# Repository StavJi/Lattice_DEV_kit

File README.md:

# Lattice DEV kit

Devkit is tested with cheap programmer from ebay. To find it try to use catchphrase ```ispDOWNLOAD Cable HW-USBN-2A```.

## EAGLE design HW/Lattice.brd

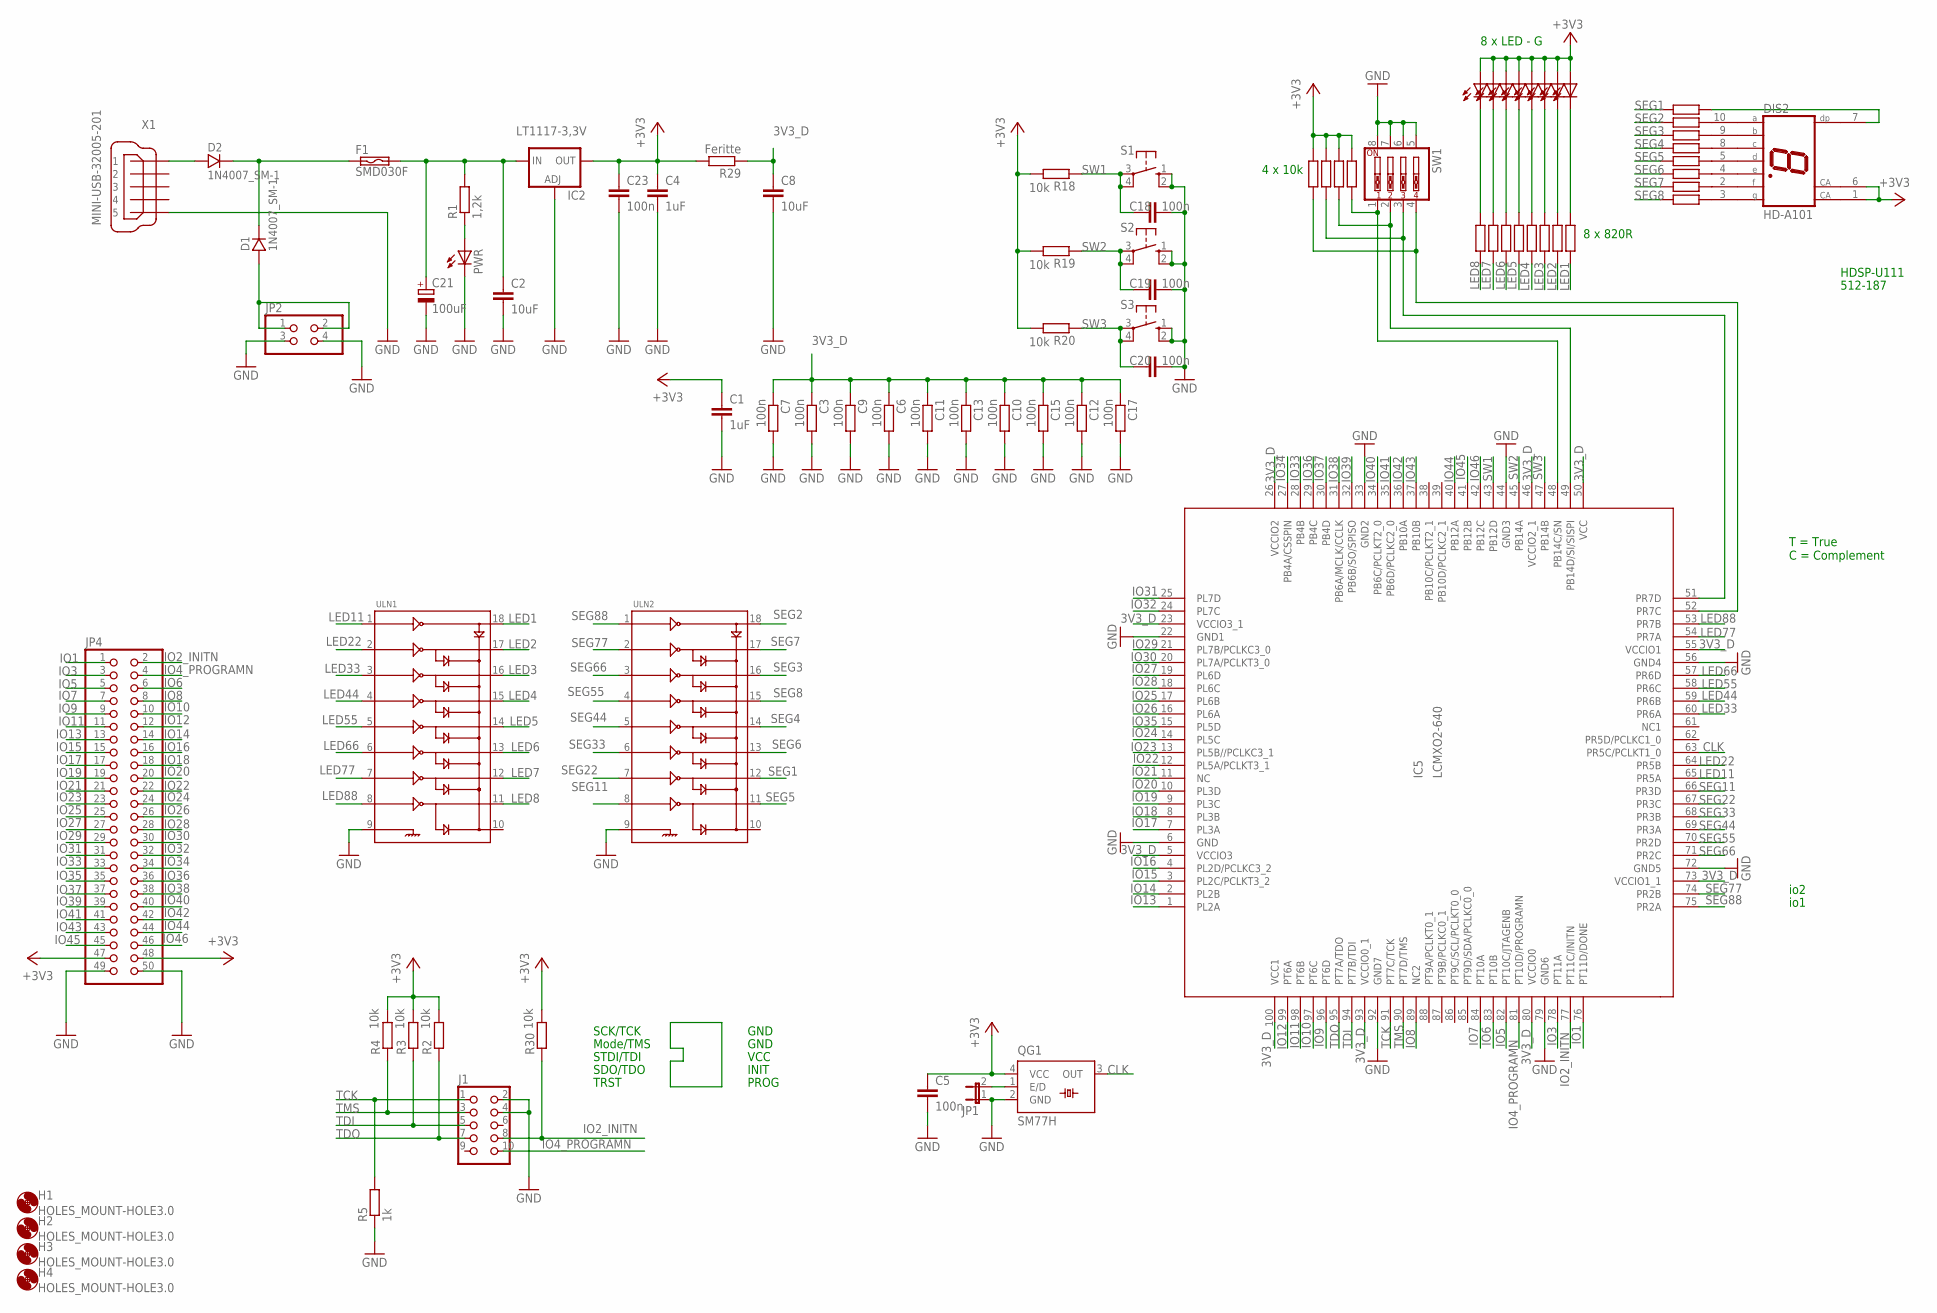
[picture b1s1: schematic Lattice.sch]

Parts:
C1, C4: 1uF; C1206
C2, C8: 10uF; C1206
C3, C6, C7, C9, C10, C11, C12, C13, C15, C17: 100n; R0603
C5, C18, C19, C20, C23: 100n; C0805
C21: 100uF; 153CLV-0605
D1, D2: 1N4007_SM-1; SM-1
DIS2: HD-A101; HDSP-A
F1: SMD030F; SMD050F
H1, H2, H3, H4: HOLES_MOUNT-HOLE3.0; HOLES_3,0
IC2: LT1117-3,3V; SOT223
IC5: LCMXO2-640; LCMX02-640
J1: CON_HEADER_2X05-PTH+SHROUDED_A; PINSHRD_PTH_2X05
JP1: JP1E; JP1
JP2: PINHD-2X2; 2X02
JP4: PINHD-2X25; 2X25
LED1, LED2, LED3, LED4, LED5, LED6, LED7, LED8: LEDSMT1206; 1206
PWR: LEDSMT1206; 1206
QG1: SM77H
R1: 1,2k; R0805
R2, R3, R4, R18, R19, R20, R30: 10k; R0805
R5: 1k; R0805
R6, R7, R8, R9, R10, R11, R12, R13, R14, R15, R16, R17, R21, R22, R23, R24, R25, R26, R27, R28: R-EU_R0805; R0805
R29: Feritte; R0805
S1, S2, S3: 10-XX; B3F-10XX
SW1: SW_DIP-4; EDG-04
ULN1, ULN2: ULN2803SOIC; SO018
X1: MINI-USB-32005-201; 32005-201

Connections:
3V3_D: C3.1, C6.1, C7.1, C8.1, C9.1, C10.1, C11.1, C12.1, C13.1, C15.1, C17.1, IC5.5 (VCCIO3), IC5.23 (VCCIO3_1), IC5.26 (VCCIO2), IC5.46 (VCCIO2_1), IC5.50 (VCC), IC5.55 (VCCIO1), IC5.73 (VCCIO1_1), IC5.80 (VCCIO0), IC5.93 (VCCIO0_1), IC5.100 (VCC1), R29.1
+3V3: C1.1, C4.1, C5.1, C23.1, DIS2.1 (CA), DIS2.6 (CA), IC2.4 (OUT), JP4.47, JP4.48, LED1.A, LED2.A, LED3.A, LED4.A, LED5.A, LED6.A, LED7.A, LED8.A, QG1.4 (VCC), R2.2, R3.2, R4.2, R14.1, R15.1, R16.1, R17.1, R18.2, R19.2, R20.2, R29.2, R30.2
CLK: IC5.63 (PR5C/PCLKT1_0), QG1.3 (OUT)
GND: C1.2, C2.2, C3.2, C4.2, C5.2, C6.2, C7.2, C8.2, C9.2, C10.2, C11.2, C12.2, C13.2, C15.2, C17.2, C18.2, C19.2, C20.2, C21.-, C23.2, IC2.1 (ADJ), IC5.6 (GND), IC5.22 (GND1), IC5.33 (GND2), IC5.44 (GND3), IC5.56 (GND4), IC5.72 (GND5), IC5.79 (GND6), IC5.92 (GND7), J1.2, J1.4, JP1.1, JP2.3, JP2.4, JP4.49, JP4.50, PWR.C, QG1.2 (GND), R5.1, S1.1 (S), S1.2 (S1), S2.1 (S), S2.2 (S1), S3.1 (S), S3.2 (S1), SW1.5, SW1.6, SW1.7, SW1.8, ULN1.9, ULN2.9, X1.5
IO1: IC5.76 (PT11D/DONE), JP4.1
IO2_INITN: IC5.77 (PT11C/INITN), J1.8, JP4.2, R30.1
IO3: IC5.78 (PT11A), JP4.3
IO4_PROGRAMN: IC5.81 (PT10D/PROGRAMN), J1.10, JP4.4
IO5: IC5.82 (PT10C/JTAGENB), JP4.5
IO6: IC5.83 (PT10B), JP4.6
IO7: IC5.84 (PT10A), JP4.7
IO8: IC5.89 (NC2), JP4.8
IO9: IC5.96 (PT6D), JP4.9
IO10: IC5.97 (PT6C), JP4.10
IO11: IC5.98 (PT6B), JP4.11
IO12: IC5.99 (PT6A), JP4.12
IO13: IC5.1 (PL2A), JP4.13
IO14: IC5.2 (PL2B), JP4.14
IO15: IC5.3 (PL2C/PCLKT3_2), JP4.15
IO16: IC5.4 (PL2D/PCLKC3_2), JP4.16
IO17: IC5.7 (PL3A), JP4.17
IO18: IC5.8 (PL3B), JP4.18
IO19: IC5.9 (PL3C), JP4.19
IO20: IC5.10 (PL3D), JP4.20
IO21: IC5.11 (NC), JP4.21
IO22: IC5.12 (PL5A/PCLKT3_1), JP4.22
IO23: IC5.13 (PL5B//PCLKC3_1), JP4.23
IO24: IC5.14 (PL5C), JP4.24
IO25: IC5.17 (PL6B), JP4.25
IO26: IC5.16 (PL6A), JP4.26
IO27: IC5.19 (PL6D), JP4.27
IO28: IC5.18 (PL6C), JP4.28
IO29: IC5.21 (PL7B/PCLKC3_0), JP4.29
IO30: IC5.20 (PL7A/PCLKT3_0), JP4.30
IO31: IC5.25 (PL7D), JP4.31
IO32: IC5.24 (PL7C), JP4.32
IO33: IC5.28 (PB4B), JP4.33
IO34: IC5.27 (PB4A/CSSPIN), JP4.34
IO35: IC5.15 (PL5D), JP4.35
IO36: IC5.29 (PB4C), JP4.36
IO37: IC5.30 (PB4D), JP4.37
IO38: IC5.31 (PB6A/MCLK/CCLK), JP4.38
IO39: IC5.32 (PB6B/SO/SPISO), JP4.39
IO40: IC5.34 (PB6C/PCLKT2_0), JP4.40
IO41: IC5.35 (PB6D/PCLKC2_0), JP4.41
IO42: IC5.36 (PB10A), JP4.42
IO43: IC5.37 (PB10B), JP4.43
IO44: IC5.40 (PB12A), JP4.44
IO45: IC5.41 (PB12B), JP4.45
IO46: IC5.42 (PB12C), JP4.46
LED1: R6.1, ULN1.18
LED2: R7.1, ULN1.17
LED3: R8.1, ULN1.16
LED4: R9.1, ULN1.15
LED5: R10.1, ULN1.14
LED6: R11.1, ULN1.13
LED7: R12.1, ULN1.12
LED8: R13.1, ULN1.11
LED11: IC5.65 (PR5A), ULN1.1
LED22: IC5.64 (PR5B), ULN1.2
LED33: IC5.60 (PR6A), ULN1.3
LED44: IC5.59 (PR6B), ULN1.4
LED55: IC5.58 (PR6C), ULN1.5
LED66: IC5.57 (PR6D), ULN1.6
LED77: IC5.54 (PR7A), ULN1.7
LED88: IC5.53 (PR7B), ULN1.8
unnamed: PWR.A, R1.1
unnamed: C2.1, C21.+, F1.2, IC2.3 (IN), R1.2
unnamed: JP1.2, QG1.1 (E/D)
unnamed: IC5.48 (PB14C/SN), R14.2, SW1.1
unnamed: DIS2.10 (A), R22.1
unnamed: DIS2.9 (B), R23.1
unnamed: DIS2.8 (C), R24.1
unnamed: DIS2.5 (D), R25.1
unnamed: DIS2.4 (E), R26.1
unnamed: LED1.C, R13.2
unnamed: LED2.C, R12.2
unnamed: LED3.C, R11.2
unnamed: LED4.C, R10.2
unnamed: LED5.C, R9.2
unnamed: LED6.C, R8.2
unnamed: LED7.C, R7.2
unnamed: LED8.C, R6.2
unnamed: DIS2.2 (F), R27.1
unnamed: IC5.51 (PR7D), R16.2, SW1.3
unnamed: DIS2.3 (G), R28.1
unnamed: DIS2.7 (DP), R21.1
unnamed: IC5.49 (PB14D/SI/SISPI), R15.2, SW1.2
unnamed: D1.A, JP2.1, JP2.2
unnamed: IC5.52 (PR7C), R17.2, SW1.4
unnamed: D1.K, D2.K, F1.1
unnamed: D2.A, X1.1
SEG1: R21.2, ULN2.12
SEG2: R22.2, ULN2.18
SEG3: R23.2, ULN2.16
SEG4: R24.2, ULN2.14
SEG5: R25.2, ULN2.11
SEG6: R26.2, ULN2.13
SEG7: R27.2, ULN2.17
SEG8: R28.2, ULN2.15
SEG11: IC5.66 (PR3D), ULN2.8
SEG22: IC5.67 (PR3C), ULN2.7
SEG33: IC5.68 (PR3B), ULN2.6
SEG44: IC5.69 (PR3A), ULN2.5
SEG55: IC5.70 (PR2D), ULN2.4
SEG66: IC5.71 (PR2C), ULN2.3
SEG77: IC5.74 (PR2B), ULN2.2
SEG88: IC5.75 (PR2A), ULN2.1
SW1: C18.1, IC5.43 (PB12D), R18.1, S1.3, S1.4 (P1)
SW2: C19.1, IC5.45 (PB14A), R19.1, S2.3, S2.4 (P1)
SW3: C20.1, IC5.47 (PB14B), R20.1, S3.3, S3.4 (P1)
TCK: IC5.91 (PT7C/TCK), J1.1, R5.2
TDI: IC5.94 (PT7B/TDI), J1.5, R3.1
TDO: IC5.95 (PT7A/TDO), J1.7, R2.1
TMS: IC5.90 (PT7D/TMS), J1.3, R4.1

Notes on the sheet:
8 x 820R
4 x 10k
8 x LED - G
T = True C = Complement
HDSP-U111
512-187
SCK/TCK
Mode/TMS
STDI/TDI
SDO/TDO
TRST
GND
VCC
INIT
PROG
io2
io1

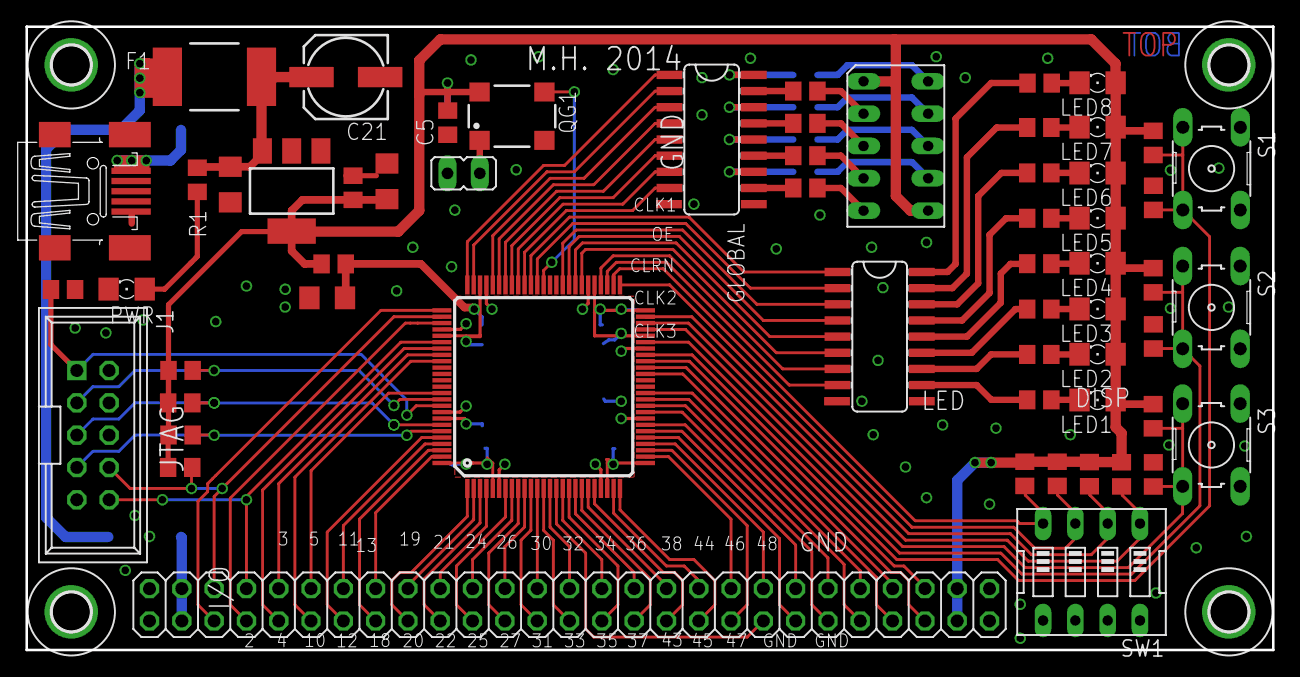
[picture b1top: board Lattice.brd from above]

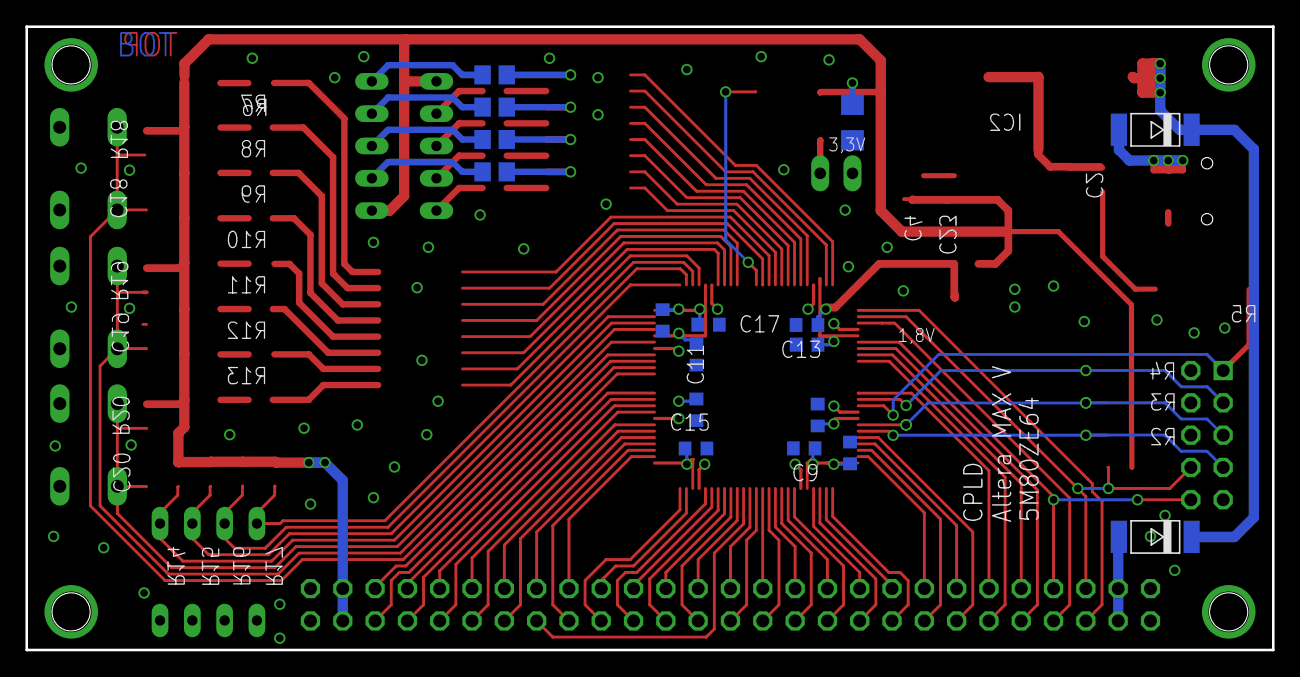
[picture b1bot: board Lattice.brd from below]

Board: 2 copper layers, 98.0 x 49.0 mm, 81 parts (17 on the bottom side), 115 nets.

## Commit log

2021-04-12 add: PCB design files and LED blinking example
2021-04-13 fix: connect programming pins prog and init, mirror schematic
2021-04-13 add photo of final product

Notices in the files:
parts and their libraries:
Copyright (C) Vlada 2004-2005
Copyright (C) PaJa 2001-2010
